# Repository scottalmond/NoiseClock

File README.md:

# NoiseClock
need to edit arduino library source files to fix bug with alpha-numeric display
xavier: sudo apt-get install arduino
NullPointer gnu.io.RXTXCommriver

git add . && git commit -m "build notes"
git push origin master

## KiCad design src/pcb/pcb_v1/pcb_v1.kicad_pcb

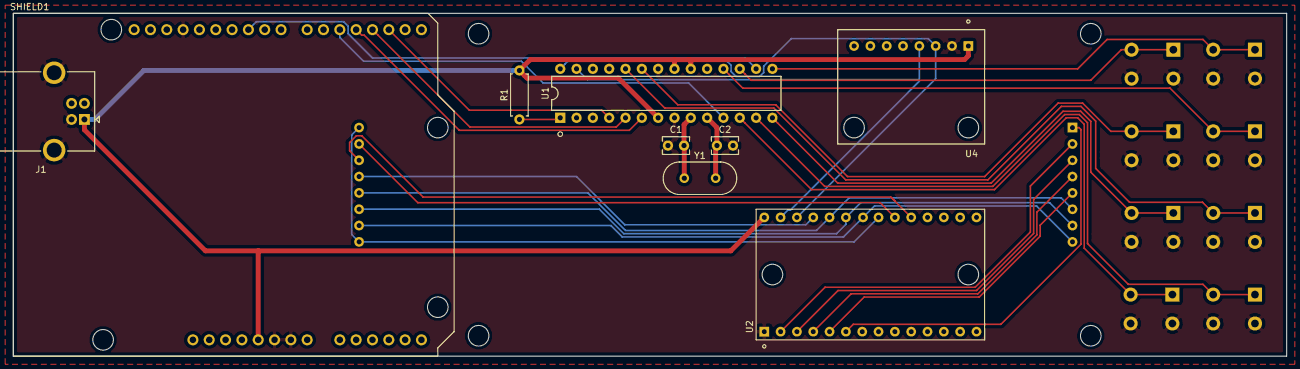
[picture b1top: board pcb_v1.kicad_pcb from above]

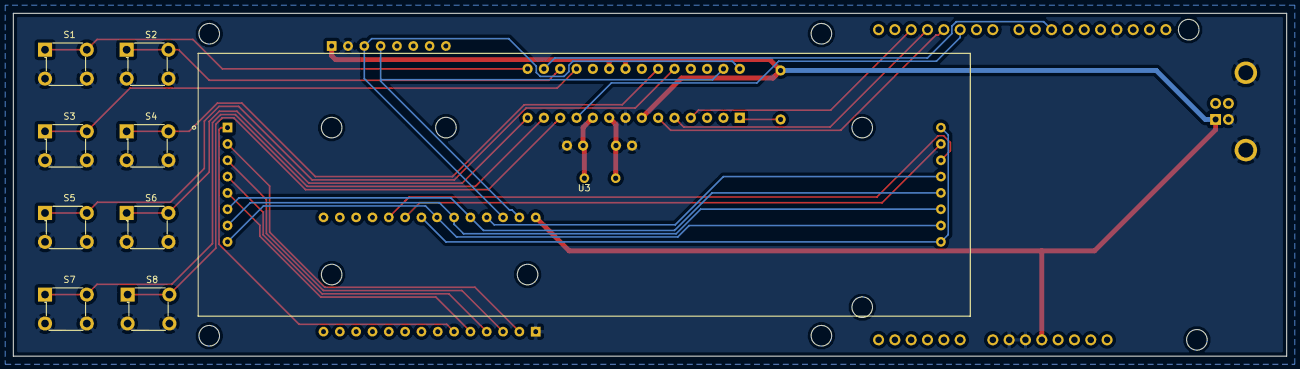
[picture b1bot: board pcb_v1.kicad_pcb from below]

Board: 2 copper layers, 198.1 x 53.3 mm, 18 parts (9 on the bottom side), 32 nets.

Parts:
C1, C2: 20pF; C_Rect_L4.0mm_W2.5mm_P2.50mm
J1: USB_B; USB_B_OST_USB-B1HSxx_Horizontal
R1: 10k; R_Axial_DIN0207_L6.3mm_D2.5mm_P7.62mm_Horizontal
S1: SONG-; Switch_Tactile_THT_6x6mm
S2: SONG+; Switch_Tactile_THT_6x6mm
S3: BR-; Switch_Tactile_THT_6x6mm
S4: BR+; Switch_Tactile_THT_6x6mm
S5: MIN-; Switch_Tactile_THT_6x6mm
S6: MIN+; Switch_Tactile_THT_6x6mm
S7: HR-; Switch_Tactile_THT_6x6mm
S8: HR+; Switch_Tactile_THT_6x6mm
SHIELD1: ARDUINO_SHIELD; Arduino_Uno_Shield
U1: ATmega328P-PU; DIP-28_W7.62mm
U2: HT16K33_breakout
U3: KW4-12041CUGA
U4: DS3231_breakout
Y1: 16MHz; Crystal_HC49-4H_Vertical

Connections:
+5V: J1.1, R1.2, SHIELD1.5VA, U1.7, U1.20, U1.21, U2.28, U4.1
BR+: S4.1, S4.2, U1.23
BR-: S3.1, S3.2, U1.18
CCS: SHIELD1.D10, U1.16
CLK: SHIELD1.D3, U1.5
COM1: U2.6, U3.1
COM2: U2.2, U3.2
COM3: U2.3, U3.3
COM4: U2.4, U3.4
COM5: U2.5, U3.5
DI: SHIELD1.D4, U1.6
GND: C1.1, C2.2, J1.4, J1.5, S1.3, S1.4, S2.3, S2.4, S3.3, S3.4, S4.3, S4.4, S5.3, S5.4, S6.3, S6.4, S7.3, S7.4, S8.3, S8.4, SHIELD1.GND1, SHIELD1.GND2, SHIELD1.GND3, U1.8, U1.22, U2.1, U4.2
HR+: S8.1, S8.2, U1.12
HR-: S7.1, S7.2, U1.13
LAT: SHIELD1.D5, U1.11
LCS: SHIELD1.D2, U1.4
MIN+: S6.1, S6.2, U1.14
MIN-: S5.1, S5.2, U1.24
unnamed: C1.2, U1.9, Y1.1
unnamed: C2.1, U1.10, Y1.2
unnamed: R1.1, U1.1
SCL: U1.28, U2.26, U4.3
SDA: U1.27, U2.27, U4.4
SEG_A: U2.25, U3.13
SEG_B_DP3-4: U2.24, U3.6, U3.12
SEG_C_DP1: U2.23, U3.7, U3.11
SEG_D_DP2: U2.22, U3.8, U3.10
SEG_E_DP5: U2.21, U3.9, U3.16
SEG_F: U2.20, U3.15
SEG_G: U2.19, U3.14
SONG+: S2.1, S2.2, U1.17
SONG-: S1.1, S1.2, U1.15

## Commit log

2019-01-13 test
2019-01-17 pictures post PCB assembly
2019-01-21 corrected schematic
2019-01-21 code cleanup
2019-01-21 cleaning up code
2019-01-21 uploaded
2019-05-30 first draft case

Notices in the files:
src/pcb/pcb_v1/pcb_v1.kicad_pcb:
License: CC BY 4.0
